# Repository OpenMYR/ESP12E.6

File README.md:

IoT Motor Hardware: Stepper
==============================
by OpenMYR

[OpenMYR Homepage](http://www.OpenMYR.com/)

Software by Brandon Brown and Kyle Berezin

Hardware design by Chris Adams

Hardware licensed under CERN Hardware License Version 1.2

Software licensed under MIT License

This repository is the source files for hardware designed to drive a stepper motor with an ESP8266-based platform.

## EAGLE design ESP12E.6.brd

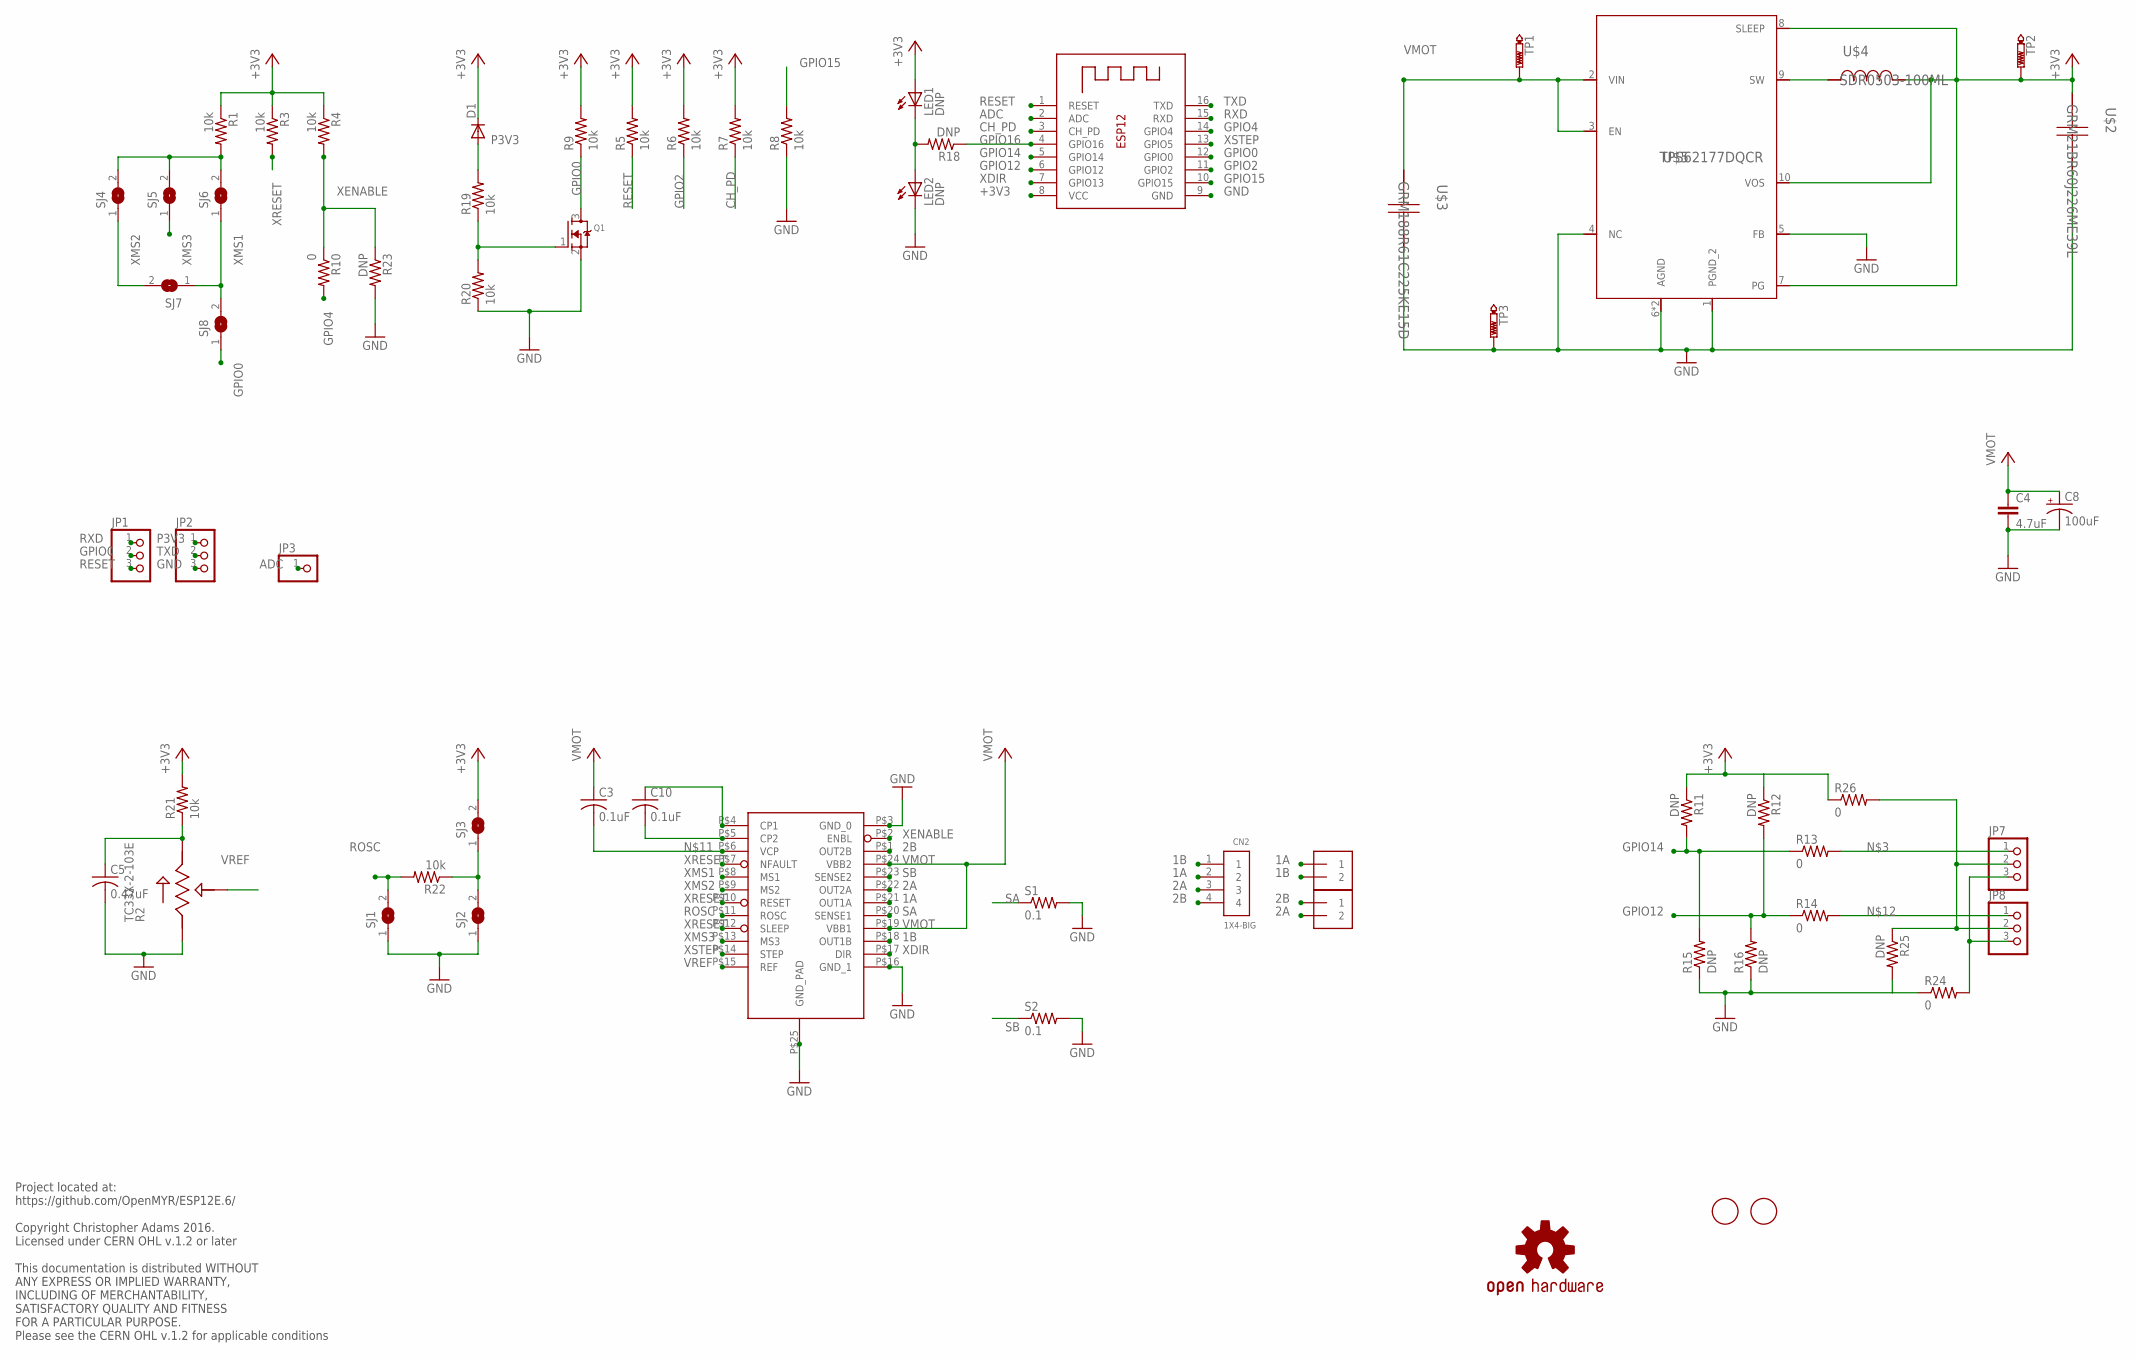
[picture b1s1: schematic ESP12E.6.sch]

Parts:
C3, C10: 0.1uF; C0603K
C4: 4.7uF; C0805
C5: 0.47uF; C0603K
C8: 100uF; PANASONIC_D
CN2: 1X4-BIG; 1X04-BIG
D1: DIODE-DO214AC; DO214AC
FD1, FD2: FIDUCIAL; FIDUCIAL_1MM
J1, J4: 1X2-3.5MM
JP1, JP2, JP7, JP8: PINHD-1X3; 1X03
JP3: PINHD-1X1CB; 1X01-CLEANBIG
LED1, LED2: DNP; CHIPLED_0603
LOGO1: OSHW-LOGOMINI; OSHW-LOGO-MINI
Q1: MOSFET-NREFLOW; SOT23
R1, R3, R4, R5, R6, R7, R8, R9, R19, R20, R21, R22: 10k; R0603
R2: TC33X-2-103E; 35WR
R10, R13, R14, R24, R26: 0; R0603
R11, R12, R15, R16, R18, R23, R25: DNP; R0603
S1, S2: 0.1; M0805
SJ1, SJ2, SJ3, SJ4, SJ5, SJ6, SJ7, SJ8: SJ
TP1, TP2, TP3: PTR1B1,27; B1,27
U1: A5984; QFN-24
U$2: GRM21BR60J226ME39L; 0805
U$3: GRM188R61C225KE15D; 0603
U$4: SDR0503-100ML; SDR0503
U$5: TPS62177DQCR; R-PWSON-N10
X1: ESP-12

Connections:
1A: CN2.2, J4.1, U1.P$21 (OUT1A)
1B: CN2.1, J4.2, U1.P$18 (OUT1B)
2A: CN2.3, J1.2, U1.P$22 (OUT2A)
2B: CN2.4, J1.1, U1.P$1 (OUT2B)
+3V3: D1.C, LED1.A, R1.1, R3.1, R4.1, R5.2, R6.2, R7.2, R9.2, R11.1, R12.1, R21.2, R26.1, SJ3.2, TP2.TP, U$2.2, U$4.2, U$5.7 (PG), U$5.8 (SLEEP), U$5.10 (VOS), X1.8 (VCC)
ADC: JP3.1, X1.2 (ADC)
CH_PD: R7.1, X1.3 (CH_PD)
GND: C4.2, C5.2, C8.-, JP2.3, LED2.C, Q1.2 (S), R2.1, R8.1, R15.1, R16.1, R20.1, R23.2, R24.1, R25.2, S1.2, S2.2, SJ1.1, SJ2.1, TP3.TP, U1.P$3 (GND_0), U1.P$16 (GND_1), U1.P$25 (GND_PAD), U$2.1, U$3.1, U$5.1 (PGND_2), U$5.4 (NC), U$5.5 (FB), U$5.6 (AGND), U$5.11 (AGND), X1.9 (GND)
GPIO0: JP1.2, Q1.3 (D), R9.1, SJ8.1, X1.12 (GPIO0)
GPIO2: R6.1, X1.11 (GPIO2)
GPIO4: R10.2, X1.14 (GPIO4)
GPIO12: R12.2, R14.1, R16.2, X1.6 (GPIO12)
GPIO14: R11.2, R13.1, R15.2, X1.5 (GPIO14)
GPIO15: R8.2, X1.10 (GPIO15)
GPIO16: R18.1, X1.4 (GPIO16)
MSN: R1.2, SJ4.2, SJ5.2, SJ6.2
unnamed: C5.1, R2.3, R21.1
unnamed: R22.1, SJ2.2, SJ3.1
unnamed: JP7.1, R13.2
unnamed: LED1.C, LED2.A, R18.2
unnamed: C10.1, U1.P$4 (CP1)
unnamed: Q1.1 (G), R19.1, R20.2
unnamed: C10.2, U1.P$5 (CP2)
unnamed: JP7.3, JP8.3, R24.2
unnamed: JP7.2, JP8.2, R25.1, R26.2
unnamed: C3.2, U1.P$6 (VCP)
unnamed: JP8.1, R14.2
unnamed: U$4.1, U$5.9 (SW)
P3V3: D1.A, JP2.1, R19.2
RESET: JP1.3, R5.1, X1.1 (RESET)
ROSC: R22.2, SJ1.2, U1.P$11 (ROSC)
RXD: JP1.1, X1.15 (RXD)
SA: S1.1, U1.P$20 (SENSE1)
SB: S2.1, U1.P$23 (SENSE2)
TXD: JP2.2, X1.16 (TXD)
VMOT: C3.1, C4.1, C8.+, TP1.TP, U1.P$19 (VBB1), U1.P$24 (VBB2), U$3.2, U$5.2 (VIN), U$5.3 (EN)
VREF: R2.2, U1.P$15 (REF)
XDIR: U1.P$17 (DIR), X1.7 (GPIO13)
XENABLE: R4.2, R10.1, R23.1, U1.P$2 (ENBL)
XMS1: SJ6.1, SJ7.1, SJ8.2, U1.P$8 (MS1)
XMS2: SJ4.1, SJ7.2, U1.P$9 (MS2)
XMS3: SJ5.1, U1.P$13 (MS3)
XRESET: R3.2, U1.P$7 (NFAULT), U1.P$10 (RESET), U1.P$12 (SLEEP)
XSTEP: U1.P$14 (STEP), X1.13 (GPIO5)

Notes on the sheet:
Project located at: https://github.com/OpenMYR/ESP12E.6/ Copyright Christopher Adams 2016. Licensed under CERN OHL v.1.2 or later This documentation is distributed WITHOUT ANY EXPRESS OR IMPLIED WARRANTY, INCLUDING OF MERCHANTABILITY, SATISFACTORY QUALITY AND FITNESS FOR A PARTICULAR PURPOSE. Pleas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

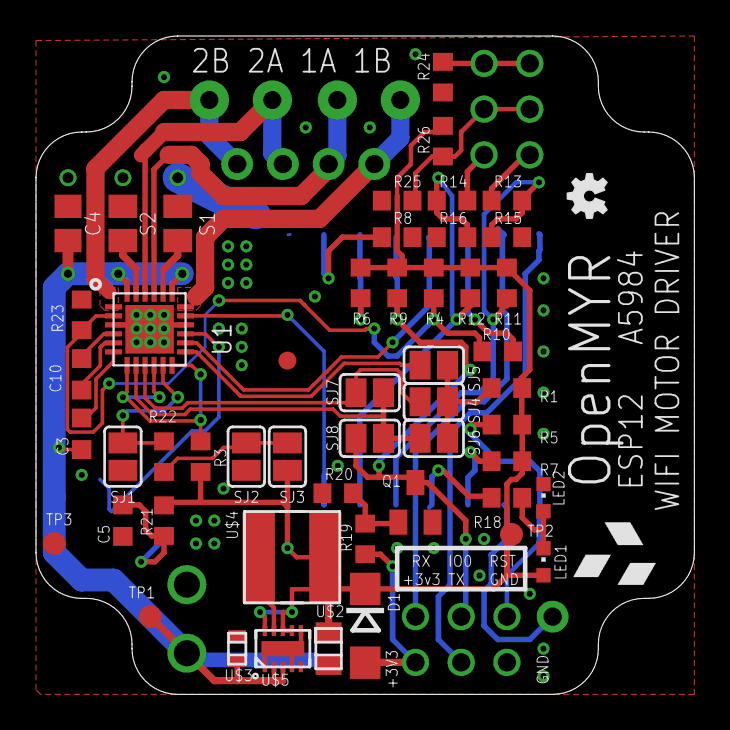
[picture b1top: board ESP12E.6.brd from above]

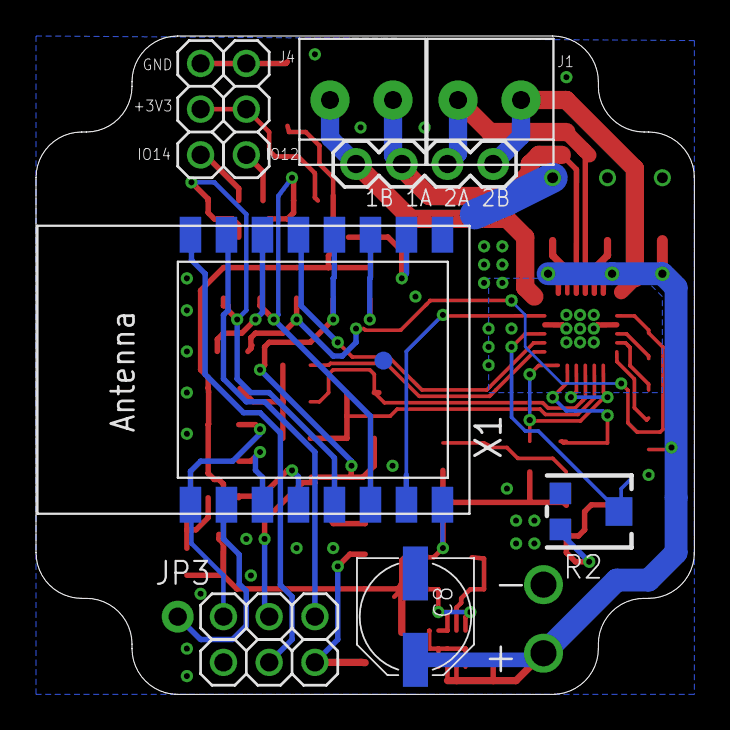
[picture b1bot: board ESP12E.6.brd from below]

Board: 2 copper layers, 36.6 x 36.6 mm, 64 parts (12 on the bottom side), 44 nets.

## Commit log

2016-04-03 :circus_tent: Added .gitattributes & .gitignore files
2016-04-03 First Commit
    Design 6:
    ESP12E with Allegro A5984
2016-04-06 GPIO pins repurposed
    GPIO 12 and 14 broken out to to pin headers for general use. Required
    that the MS section of board to be modified. GPIO0 now can control step
    mode between 0 and 32 micro-stepping.
2016-04-06 Additional Ignore files
    Added *.pro files to ignore file.
2016-05-08 Buck Regulator
    Prototype +3.3V DC buck regultaor. Based around TI TPS62177 IC.
2016-07-09 License Update
    Licensed under CERN OHL v.1.2 or later
2016-08-28 Power Isolation
    Separation between VMOT/+3V3 and +3V3/GND nets is increased. Rearranged
    R3,R21, U$3 and, U$2.
    Removed U$1 in the regulator schematic as it was not nessesary.
2016-10-15 PDF schematic generated
    PDF schematic added into Docs folder. Sch file modified to have
    schematic more presentable.
2018-05-20 //Lowered power via hole sizes to 18 AWG // Added ADC pin exposure
2018-05-24 PDF schematic updated
2018-10-18 Oct Update
    Power drill size change and placment of IO pin resistors
2018-11-23 A5984 QFN24
    Layout with QFN24 driver
2018-11-23 Updated Sch PDF
2018-11-23 KiCAD import with optimization
    ESP12.6 imported to KiCAD with A5984 QFN24 package and resistor array optimization.
2018-11-23 Update and added tracked files
2018-11-29 Removed solder paste from solder jumpers

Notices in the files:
parts and their libraries:
SparkFun-Aesthetics: Licensing: Creative Commons ShareAlike 4.0 International - https://creativecommons.org/licenses/by-sa/4.0
